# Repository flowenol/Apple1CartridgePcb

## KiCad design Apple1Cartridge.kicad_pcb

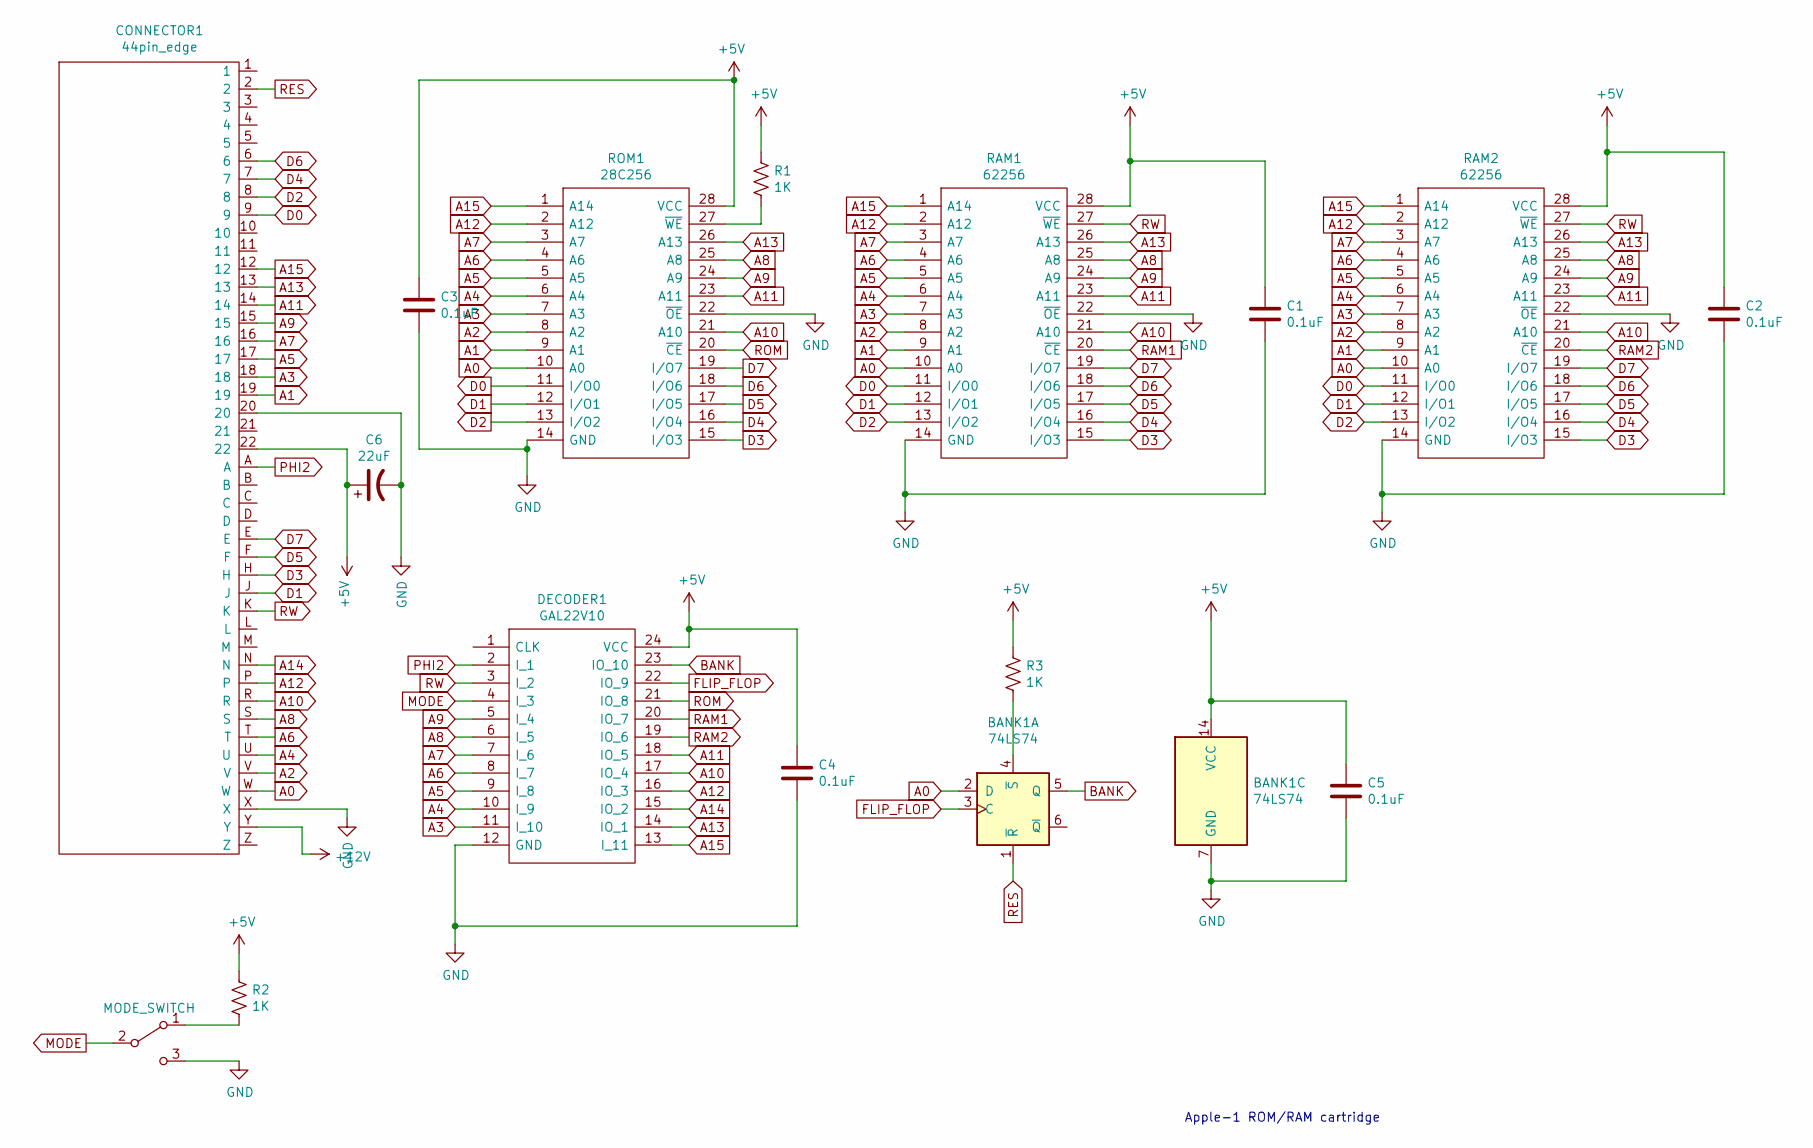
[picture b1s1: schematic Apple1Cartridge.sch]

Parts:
BANK1: 74LS74; DIP-14_W7.62mm_LongPads
C1, C2, C3, C4, C5: 0.1uF; C_Disc_D5.0mm_W2.5mm_P2.50mm
C6: 22uF; CP_Radial_D4.0mm_P2.00mm
CONNECTOR1: 44pin_edge; 44pin1
DECODER1: GAL22V10; DIP-24_W7.62mm_LongPads; Manufacturer_Part_Number GAL22V10-15LP
MODE_SWITCH1: MODE_SWITCH; PinHeader_1x03_P2.54mm_Vertical
R1, R2, R3: 1K; R_Axial_DIN0207_L6.3mm_D2.5mm_P7.62mm_Horizontal
RAM1: 62256; DIP-28_W15.24mm_LongPads
RAM2: 62256; DIP-28_W15.24mm
ROM1: 28C256; DIP-28_W15.24mm_LongPads

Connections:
+5V: BANK1.14 (VCC), C1.1, C2.1, C3.1, C4.1, C5.1, C6.1, CONNECTOR1.22, DECODER1.24 (VCC), R1.1, R2.1, R3.1, RAM1.28 (VCC), RAM2.28 (VCC), ROM1.28 (VCC)
+12V: CONNECTOR1.Y
A0: BANK1.2 (D), CONNECTOR1.W, RAM1.10 (A0), RAM2.10 (A0), ROM1.10 (A0)
A1: CONNECTOR1.19, RAM1.9 (A1), RAM2.9 (A1), ROM1.9 (A1)
A2: CONNECTOR1.V, RAM1.8 (A2), RAM2.8 (A2), ROM1.8 (A2)
A3: CONNECTOR1.18, DECODER1.11 (I_10), RAM1.7 (A3), RAM2.7 (A3), ROM1.7 (A3)
A4: CONNECTOR1.U, DECODER1.10 (I_9), RAM1.6 (A4), RAM2.6 (A4), ROM1.6 (A4)
A5: CONNECTOR1.17, DECODER1.9 (I_8), RAM1.5 (A5), RAM2.5 (A5), ROM1.5 (A5)
A6: CONNECTOR1.T, DECODER1.8 (I_7), RAM1.4 (A6), RAM2.4 (A6), ROM1.4 (A6)
A7: CONNECTOR1.16, DECODER1.7 (I_6), RAM1.3 (A7), RAM2.3 (A7), ROM1.3 (A7)
A8: CONNECTOR1.S, DECODER1.6 (I_5), RAM1.25 (A8), RAM2.25 (A8), ROM1.25 (A8)
A9: CONNECTOR1.15, DECODER1.5 (I_4), RAM1.24 (A9), RAM2.24 (A9), ROM1.24 (A9)
A10: CONNECTOR1.R, DECODER1.17 (IO_4), RAM1.21 (A10), RAM2.21 (A10), ROM1.21 (A10)
A11: CONNECTOR1.14, DECODER1.18 (IO_5), RAM1.23 (A11), RAM2.23 (A11), ROM1.23 (A11)
A12: CONNECTOR1.P, DECODER1.16 (IO_3), RAM1.2 (A12), RAM2.2 (A12), ROM1.2 (A12)
A13: CONNECTOR1.13, DECODER1.14 (IO_1), RAM1.26 (A13), RAM2.26 (A13), ROM1.26 (A13)
A14: CONNECTOR1.N, DECODER1.15 (IO_2)
A15: CONNECTOR1.12, DECODER1.13 (I_11), RAM1.1 (A14), RAM2.1 (A14), ROM1.1 (A14)
BANK: BANK1.5 (Q), DECODER1.23 (IO_10)
D0: CONNECTOR1.9, RAM1.11 (I/O0), RAM2.11 (I/O0), ROM1.11 (I/O0)
D1: CONNECTOR1.J, RAM1.12 (I/O1), RAM2.12 (I/O1), ROM1.12 (I/O1)
D2: CONNECTOR1.8, RAM1.13 (I/O2), RAM2.13 (I/O2), ROM1.13 (I/O2)
D3: CONNECTOR1.H, RAM1.15 (I/O3), RAM2.15 (I/O3), ROM1.15 (I/O3)
D4: CONNECTOR1.7, RAM1.16 (I/O4), RAM2.16 (I/O4), ROM1.16 (I/O4)
D5: CONNECTOR1.F, RAM1.17 (I/O5), RAM2.17 (I/O5), ROM1.17 (I/O5)
D6: CONNECTOR1.6, RAM1.18 (I/O6), RAM2.18 (I/O6), ROM1.18 (I/O6)
D7: CONNECTOR1.E, RAM1.19 (I/O7), RAM2.19 (I/O7), ROM1.19 (I/O7)
FLIP_FLOP: BANK1.3 (C), DECODER1.22 (IO_9)
GND: BANK1.7 (GND), C1.2, C2.2, C3.2, C4.2, C5.2, C6.2, CONNECTOR1.20, CONNECTOR1.X, DECODER1.12 (GND), MODE_SWITCH1.3 (C), RAM1.14 (GND), RAM1.22 (~OE), RAM2.14 (GND), RAM2.22 (~OE), ROM1.14 (GND), ROM1.22 (~OE)
MODE: DECODER1.4 (I_3), MODE_SWITCH1.2 (B)
unnamed: BANK1.4 (~S), R3.2
unnamed: MODE_SWITCH1.1 (A), R2.2
unnamed: R1.2, ROM1.27 (~WE)
PHI2: CONNECTOR1.A, DECODER1.2 (I_1)
RAM1: DECODER1.20 (IO_7), RAM1.20 (~CE)
RAM2: DECODER1.19 (IO_6), RAM2.20 (~CE)
RES: BANK1.1 (~R), CONNECTOR1.2
ROM: DECODER1.21 (IO_8), ROM1.20 (~CE)
RW: CONNECTOR1.K, DECODER1.3 (I_2), RAM1.27 (~WE), RAM2.27 (~WE)

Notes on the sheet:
Apple-1 ROM/RAM cartridge

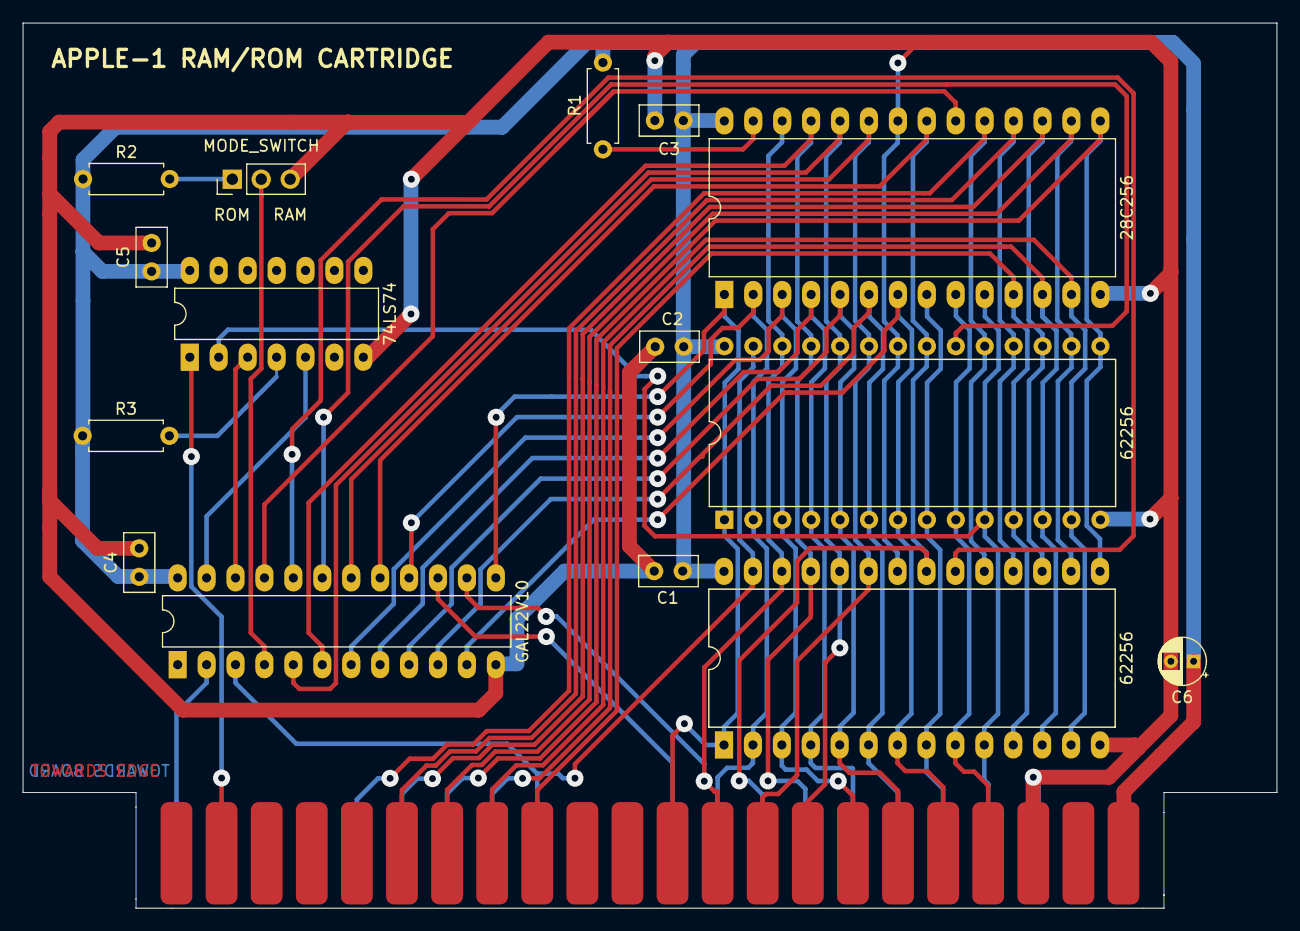
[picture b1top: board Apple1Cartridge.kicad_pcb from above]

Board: 2 copper layers, 110.1 x 77.7 mm, 16 parts (0 on the bottom side), 38 nets.

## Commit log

2021-03-03 Added .gitignore
2021-03-04 Fixed element values on schematics
